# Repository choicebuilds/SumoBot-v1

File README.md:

# SumoBot v1
Two weeks - that was the time I had to go from absolutely nothing to a fully-functioning robot to participate in the upcoming competition in Orlando, Florida. At the time, it took JLCPCB 4 weeks to ship a PCB to the US even with rushed shipping due to delayed customs; so, I decided to make everything inside our makerspace - The Hive.
  
Thanks to my wonderful peers and the knowledge gained throughout my time at Georgia Tech, I learned how to use KiCAD, fabricate the PCB using the LPKF Protomat/Protolaser, and through-hole solder all the components. The chassis of the robot was designed by a wonderful teammate on the mechanical side. This version was merely a rushed proof of concept for the upcoming competition (if you read on, you will see the various limitations I faced and how I combatted them for the time being). A significantly more complex, 4-layer PCB that addressed all the issues along with quality of life updates have been created the following semester: [SumoBot v2](https://github.com/choicebuilds/SumoBot-v2)!

## Schematic
Since I only had two weeks, my goal was to add only the bare minimum components for a functional robot. This consisted of a distance sensor to detect the other sumobot, a line sensor to detect whether we were out of bounds or not, a motor driver to drive the wheels, a power system, and status LEDs for debugging. The arduino nano was small and sufficient for my needs; here is my very first schematic:  
  
With the distance sensors and line sensors being abstracted as an attachable module, it was easy to determine which footprints to use since it was either a screw terminal to attach said sensors or female pins to insert the arduino and the motor driver. However, the only issue was power. While I could have used a buck converter, I figured for simplicity sake, I would use a MOSFET that basically dissipated excess voltage into heat, allowing it to supply 5V to the entire system. The advantage here was that I could actually connect the battery's 9V directly into the motors so that while the system got the 5V it needed, the motors could go overdrive at 9V.  

### Issue #1
This is where I ran into my first issue: as simple as the Arduino Nano was to use, if I hogged 7 pins for status LEDs (5 for distance and 2 for line), I ran out of GPIO pins to use for the motor driver. Considering I had two weeks left, I did not have a time to come up with a complex strategy. So, I just tied AI1 and BI1 to 5V and AI2 and BI2 to GND (along with STBY to 5V), which saved me THREE pins. The only drawback was the fact that I could not move backwards; however, depending on the values of PWMA (left motor) and PWMB (right motor), I could control the speed and spin around as needed.  

## Fabrication
While I found it super cool that I could literally fabricate a PCB inside our makerspace, I soon figured out why nobody actually used the machines: it was plagued with a lot of limitations and lack of experience. Considering the fact that none of the peer instructors (other than one passionate master PI who I cannot thank enough) knew how to use the machines and I only had a book to go off of, I ran into a lot of minor inconveniences and setbacks. However, I will filter out the noise and only highlight the limitations of the final product (i.e. I won't get into nontechnical issues such as alignment as shown below):  

### Issue #2
While the LPKF Protomat and Protolaser could technically make a functional PCB, there was no way to make vias (non-plated drilling). In other words, I could not connect the front layer to the back layer unless I manually connected them via soldering both sides with a wire, which turned out to be a very big inconvenience. So, I had to connect all my traces from VCC to GND to all GPIO pins into the back layer so that when I through-hole soldered everything, the objects would be on the top layer and the soldering will all be done on the bottom layer. Keep in mind, the places where I placed screw terminals and female connectors pins were physically obstructed by the object itself, so if I ever wanted to connect layer 1 to layer 2, I had to create vias to the side, as shown in one of my failed iterations:  

### Issue #3
Now you may be wondering: aren't PCBs usually green? Well, that's because my PCBs lacked a solder mask since our makerspace did not have a machine to create them; that also included silkscreens so I had to physically laser out the copper using the laser of the LPKF Protolaser for any text. This made it an absolute nightmare for continuity testing because I kept getting shorts to the GND plane, which was on the same layer as all my connections.  

### Issue #4
This is more of an advanced topic that didn't detrimentally affect the robot, but considering my PCB virtually had zero decoupling capacitors and no dedicated power planes, the whole power network was more susceptible to power supply noise and EMI. Luckily, I did create a ground pour on the unused area and tried to connect a few wires into the other layer for a giant GND plane for heat dissipation on the motors, it was by no means optimal. This issue was fixed during my second iteration in SumoBot v2, but this really was just a proof of concept in the end. Not to mention, 90 degrees traces weren't exactly good practice due to impedance discontinuities, while negligible for my use robot:  

### Issue #5
Also, A7 is an analog input only pin. While it doesn't affect functionality, you would not see the LED flash.

## The Actual Process
Now fabrication is actually very simple: you import you gerber files (front layer copper layout, back layer copper layout, edge cuts, and drill files) and use the LPKF Protomat to drill the holes:  
  
Then you remove the unwanted copper using the LPKF Protolaser:  
  
And back to the LPKF Protomat to cut out the board itself from the bigger sheet of copper:  
  
Thanks to many failed iterations that allowed me to practice soldering, I was able to complete the board! With careful continuity testing, it was ready to be mounted onto the mechanical chassis.  

## Mechanical & Firmware
Our makerspace had a plethora of 3D printers. One freshman mechanical teammate was diligent and ambitious enough to create the chassis for us in the limited time that we had; here is are a few pictures:  
  
Due to it being a public repository, I have only included the basic code for a functional robot. Complex state machines and algorithms used during the competition are excluded.

## Working Demo
While we were a group of five, the whole robot was essentially created by me and the mechanical teammate. Here is a working demo of our robot with my functional PCB:

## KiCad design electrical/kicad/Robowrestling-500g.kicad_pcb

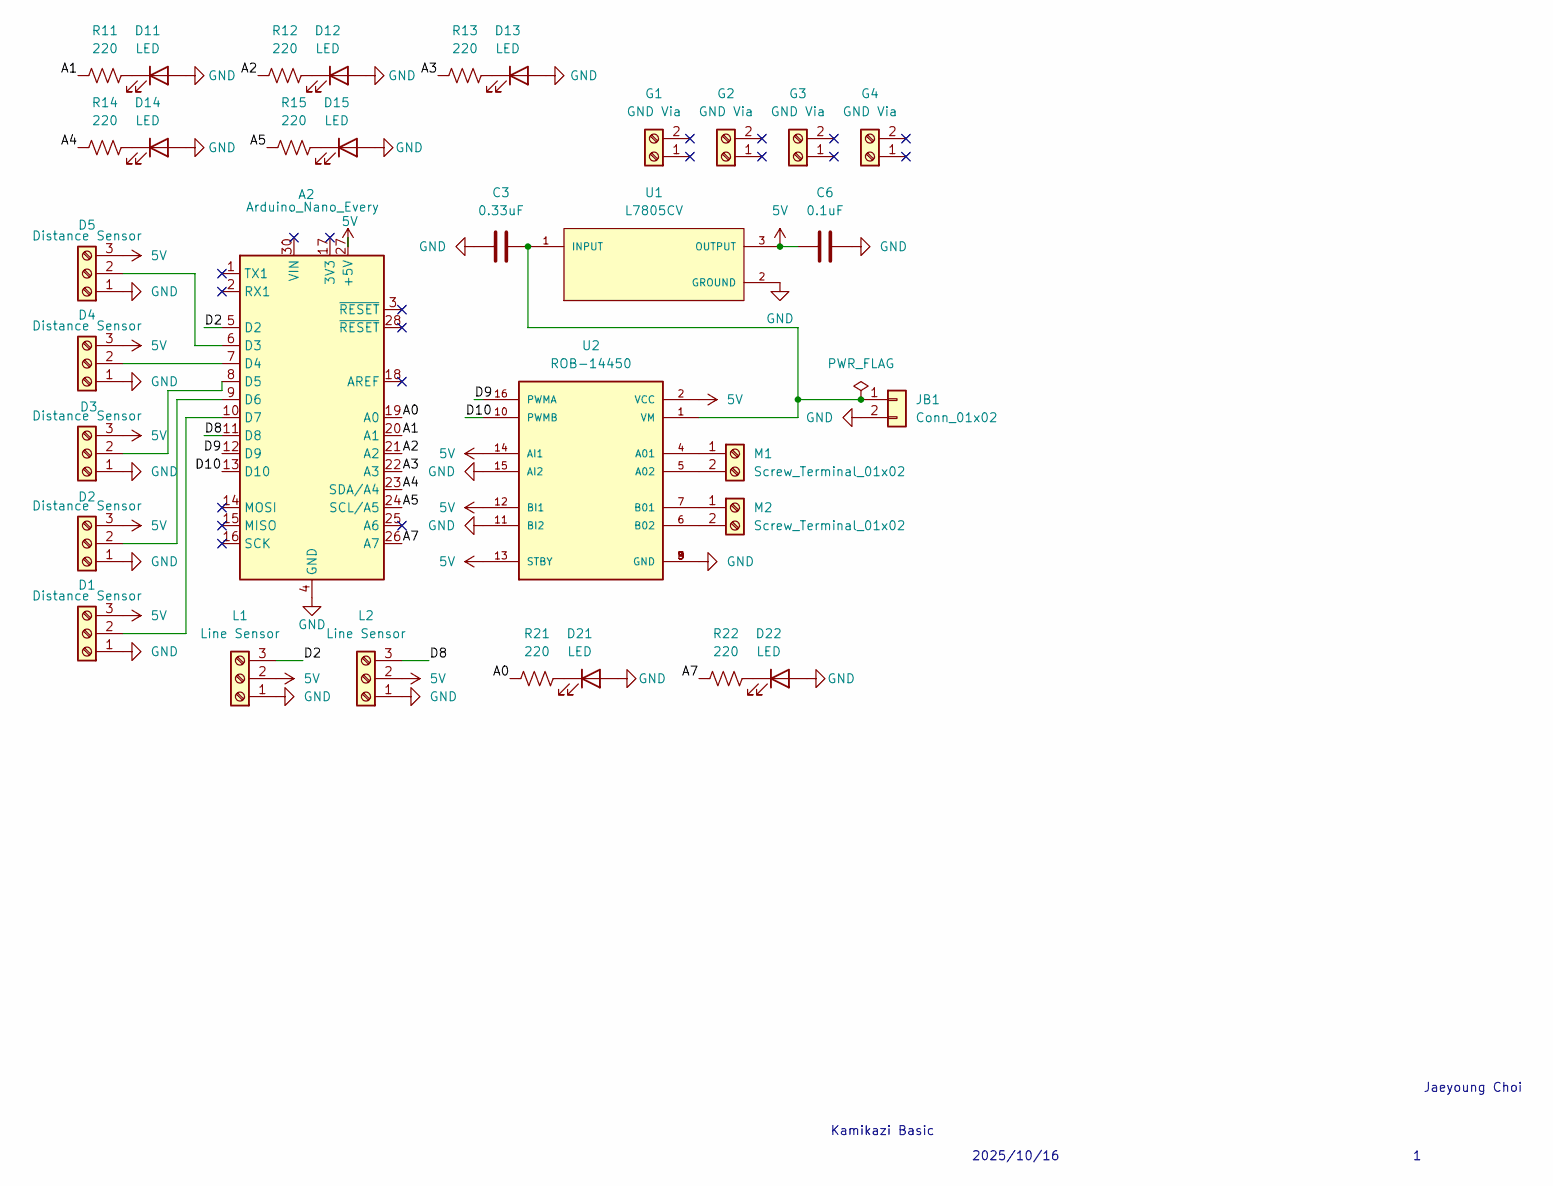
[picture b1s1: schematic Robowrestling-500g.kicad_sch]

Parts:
A2: Arduino_Nano_Every; Arduino_Nano
C3: 0.33uF; C_Disc_D3.0mm_W1.6mm_P2.50mm
C6: 0.1uF; C_Disc_D3.0mm_W1.6mm_P2.50mm
D1, D2, D3, D4, D5: Distance Sensor; TerminalBlock_Xinya_XY308-2.54-3P_1x03_P2.54mm_Horizontal
D11, D12, D13, D14, D15, D21, D22: LED; LED_D5.0mm
G1, G2, G3, G4: GND Via; TerminalBlock_Xinya_XY308-2.54-2P_1x02_P2.54mm_Horizontal
JB1: Conn_01x02; AMASS_XT30U-F_1x02_P5.0mm_Vertical
L1, L2: Line Sensor; TerminalBlock_Xinya_XY308-2.54-3P_1x03_P2.54mm_Horizontal
M1, M2: Screw_Terminal_01x02; TerminalBlock_Xinya_XY308-2.54-2P_1x02_P2.54mm_Horizontal
R11, R12, R13, R14, R15, R21, R22: 220; R_Axial_DIN0207_L6.3mm_D2.5mm_P7.62mm_Horizontal
U1: L7805CV; TO255P1040X460X1968-3; PARTREV 36
U2: ROB-14450; MODULE_ROB-14450; PARTREV 11-13-17

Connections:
5V: A2.27 (+5V), C6.1, D1.3, D2.3, D3.3, D4.3, D5.3, L1.2, L2.2, U1.3 (OUTPUT), U2.2 (VCC), U2.12 (BI1), U2.13 (STBY), U2.14 (AI1)
/A0: A2.19 (A0), R21.1
/A1: A2.20 (A1), R11.1
/A2: A2.21 (A2), R12.1
/A3: A2.22 (A3), R13.1
/A4: A2.23 (SDA/A4), R14.1
/A5: A2.24 (SCL/A5), R15.1
/A7: A2.26 (A7), R22.1
/D2: A2.5 (D2), L1.3
/D8: A2.11 (D8), L2.3
/D9: A2.12 (D9), U2.16 (PWMA)
/D10: A2.13 (D10), U2.10 (PWMB)
GND: A2.4 (GND), A2.29 (GND), C3.1, C6.2, D1.1, D2.1, D3.1, D4.1, D5.1, D11.2 (A), D12.2 (A), D13.2 (A), D14.2 (A), D15.2 (A), D21.2 (A), D22.2 (A), JB1.2, L1.1, L2.1, U1.2 (GROUND), U2.3 (GND), U2.8 (GND), U2.9 (GND), U2.11 (BI2), U2.15 (AI2)
unnamed: A2.6 (D3), D5.2
unnamed: A2.7 (D4), D4.2
unnamed: A2.8 (D5), D3.2
unnamed: A2.9 (D6), D2.2
unnamed: A2.10 (D7), D1.2
unnamed: D11.1 (K), R11.2
unnamed: D12.1 (K), R12.2
unnamed: D13.1 (K), R13.2
unnamed: D14.1 (K), R14.2
unnamed: D15.1 (K), R15.2
unnamed: D21.1 (K), R21.2
unnamed: D22.1 (K), R22.2
unnamed: C3.2, JB1.1, U1.1 (INPUT), U2.1 (VM)
unnamed: M1.1, U2.4 (A01)
unnamed: M1.2, U2.5 (A02)
unnamed: M2.1, U2.7 (B01)
unnamed: M2.2, U2.6 (B02)

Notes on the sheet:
Kamikazi Basic
Jaeyoung Choi
2025/10/16

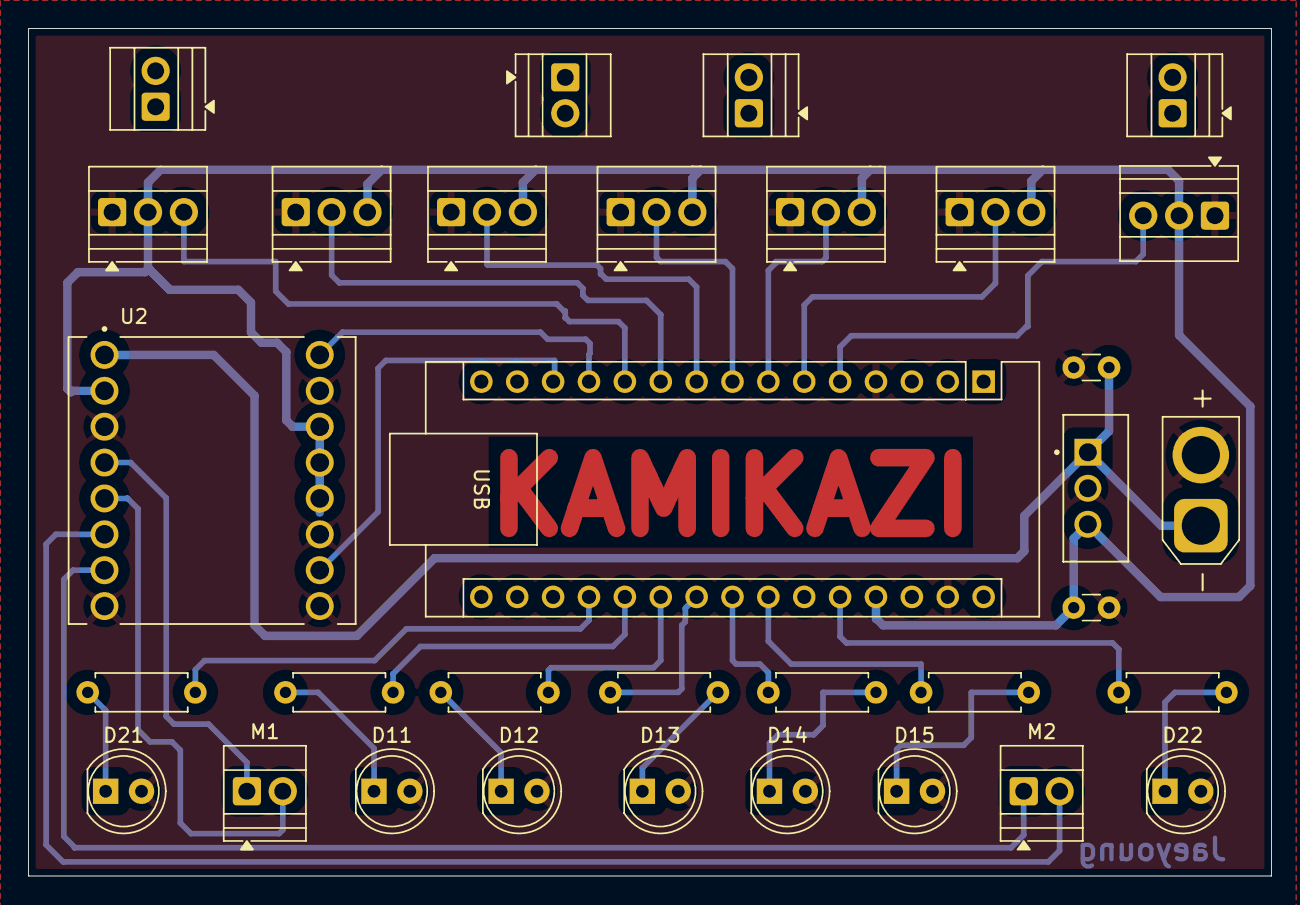
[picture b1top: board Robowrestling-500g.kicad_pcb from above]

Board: 4 copper layers, 88.0 x 60.0 mm, 33 parts (0 on the bottom side), 30 nets.
